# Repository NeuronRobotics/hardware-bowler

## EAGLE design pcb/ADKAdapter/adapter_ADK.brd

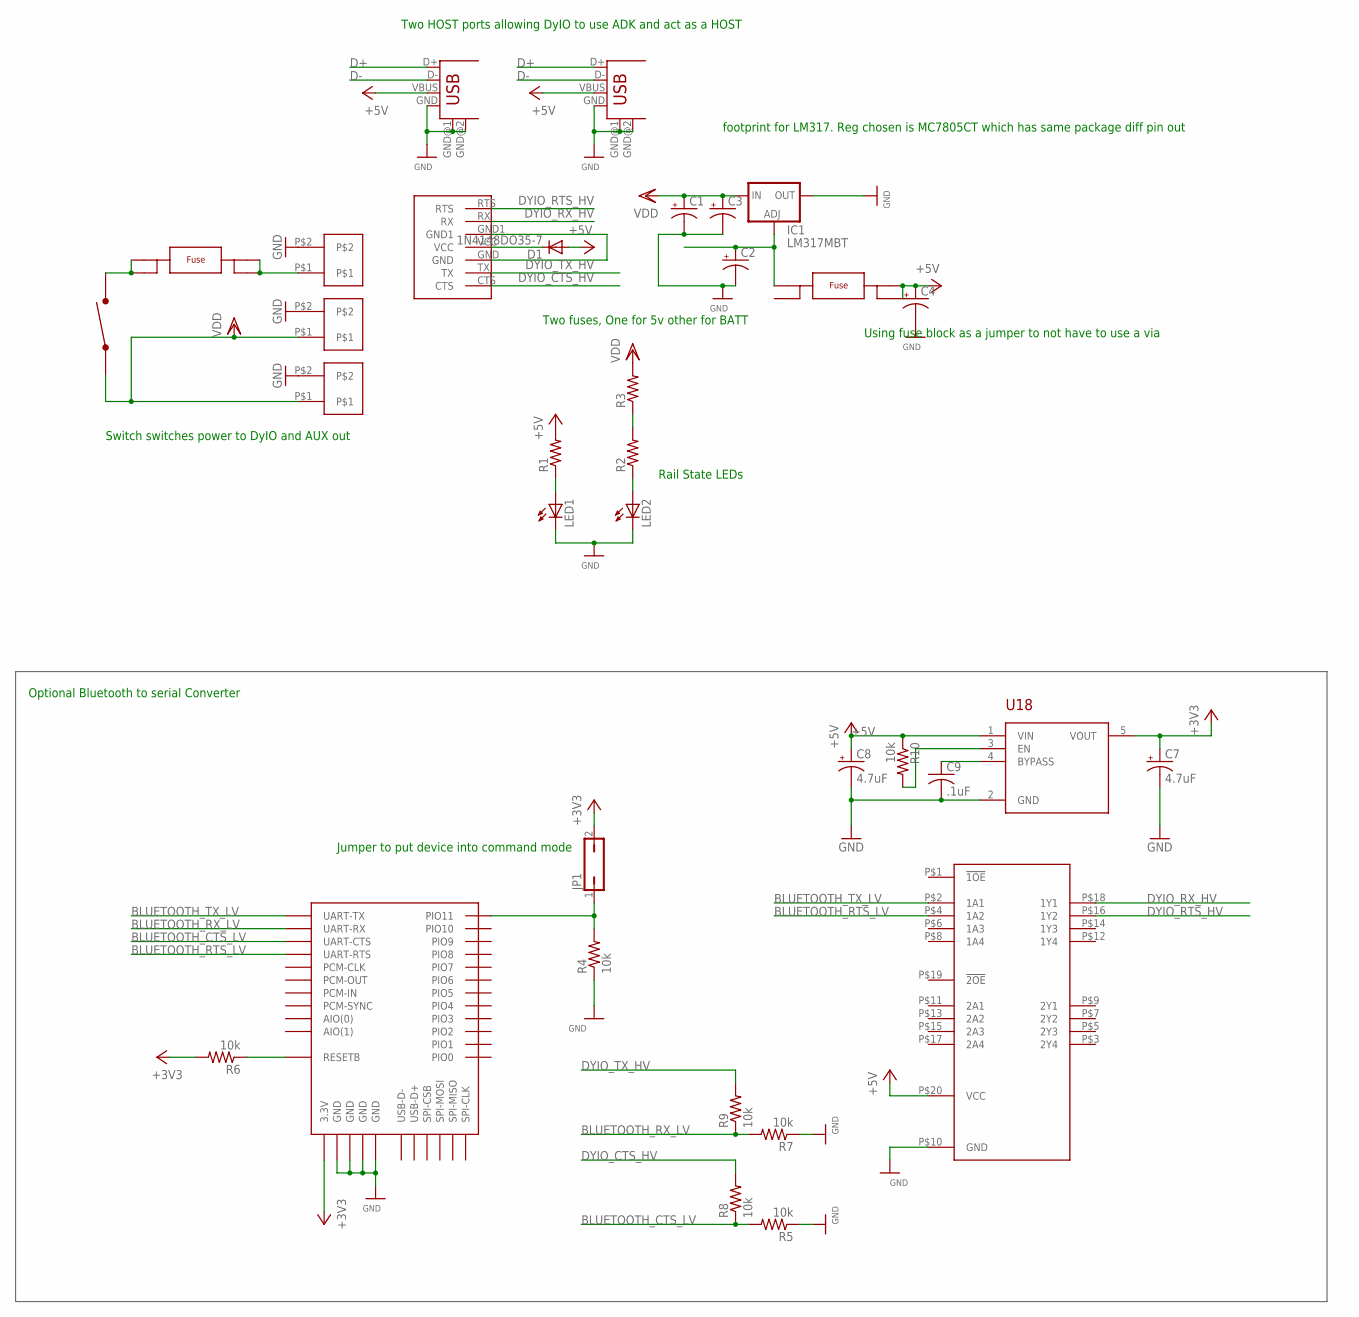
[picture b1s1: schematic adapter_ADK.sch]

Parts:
C1, C2, C3, C4: CPOL-USE2.5-5; E2,5-5
C7, C8: 4.7uF; R/2012-12R
C9: .1uF; C0402
D1: 1N4148DO35-7; DO35-7
IC1: LM317MBT; TO220L1
JP1: JP1Q; JP1
LED1, LED2: LED5MM
R1, R2, R3: R-US_0204/2V; 0204V
R4, R5, R6, R7, R8, R9: 10k; R0603
R10: 10k; R0402
U18: LDS3985XX33; SOT23-5
U$1, U$2: FUSE520; FUSE-520
U$3, U$4, U$19: 2P; 2PTH
U$5: SPST; SW331-ND
U$6: BTM400_6B
U$7: SN74ACT24; R-PDS0-G20
U$10: WASP7PIN
USB1, USB2: USB-A-H

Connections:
+3V3: C7.+, JP1.2, R6.2, U18.5 (VOUT), U$6.3.3V
+5V: C4.+, C8.+, D1.A, R1.2, R10.1, U18.1 (VIN), U$2.F2A, U$2.F2B, U$7.P$20 (VCC), USB1.VBUS, USB2.VBUS
BLUETOOTH_CTS_LV: R5.2, R8.1, U$6.UART-CTS
BLUETOOTH_RTS_LV: U$6.UART-RTS, U$7.P$4 (1A2)
BLUETOOTH_RX_LV: R7.2, R9.1, U$6.UART-RX
BLUETOOTH_TX_LV: U$6.UART-TX, U$7.P$2 (1A1)
CFG: JP1.1, R4.2, U$6.PIO(11) (PIO11)
D+: USB1.D+, USB2.D+
D-: USB1.D-, USB2.D-
DYIO_CTS_HV: R8.2, U$10.CTS
DYIO_RTS_HV: U$7.P$16 (1Y2), U$10.RTS
DYIO_RX_HV: U$7.P$18 (1Y1), U$10.RX
DYIO_TX_HV: R9.2, U$10.TX
GND: C1.-, C2.-, C3.-, C4.-, C7.-, C8.-, C9.2, IC1.2 (OUT), LED1.K (C), LED2.K (C), R4.1, R5.1, R7.1, U18.2 (GND), U$3.P$2, U$4.P$2, U$6.GND@1 (GND), U$6.GND@2 (GND), U$6.GND@3 (GND), U$6.GND@4 (GND), U$7.P$10 (GND), U$10.GND, U$10.GND1, U$19.P$2, USB1.GND, USB1.GND@1 (GND), USB1.GND@2 (GND), USB2.GND, USB2.GND@1 (GND), USB2.GND@2 (GND)
unnamed: U$1.F1A, U$1.F1B, U$5.SW2
unnamed: U$1.F2A, U$1.F2B, U$3.P$1
unnamed: LED1.A, R1.1
unnamed: C2.+, IC1.1 (ADJ), U$2.F1A
unnamed: LED2.A, R2.1
unnamed: R2.2, R3.1
unnamed: D1.C, U$10.VCC
unnamed: R6.1, U$6.RESETB
unnamed: R10.2, U18.3 (EN)
unnamed: C9.1, U18.4 (BYPASS)
VDD: C1.+, C3.+, IC1.3 (IN), R3.2, U$4.P$1, U$5.SW1, U$19.P$1

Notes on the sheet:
Two fuses, One for 5v other for BATT
Two HOST ports allowing DyIO to use ADK and act as a HOST
footprint for LM317. Reg chosen is MC7805CT which has same package diff pin out
Using fuse block as a jumper to not have to use a via
Switch switches power to DyIO and AUX out
Rail State LEDs
Optional Bluetooth to serial Converter
Jumper to put device into command mode

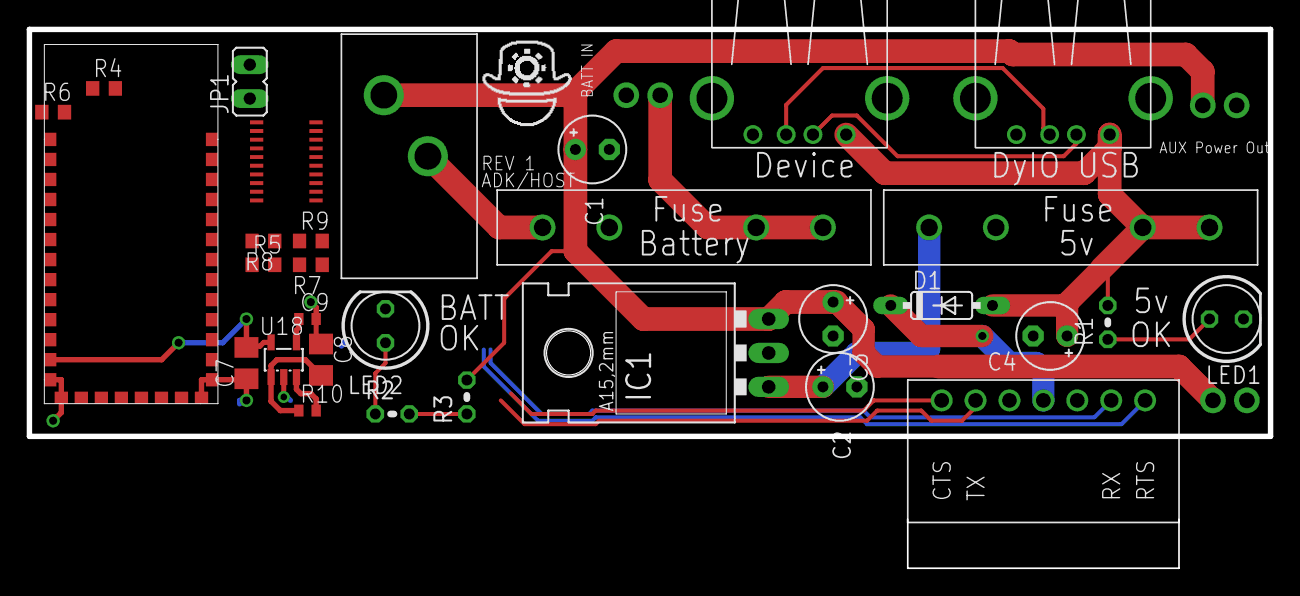
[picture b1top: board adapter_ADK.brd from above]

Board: 2 copper layers, 93.0 x 30.5 mm, 34 parts (0 on the bottom side), 25 nets.
